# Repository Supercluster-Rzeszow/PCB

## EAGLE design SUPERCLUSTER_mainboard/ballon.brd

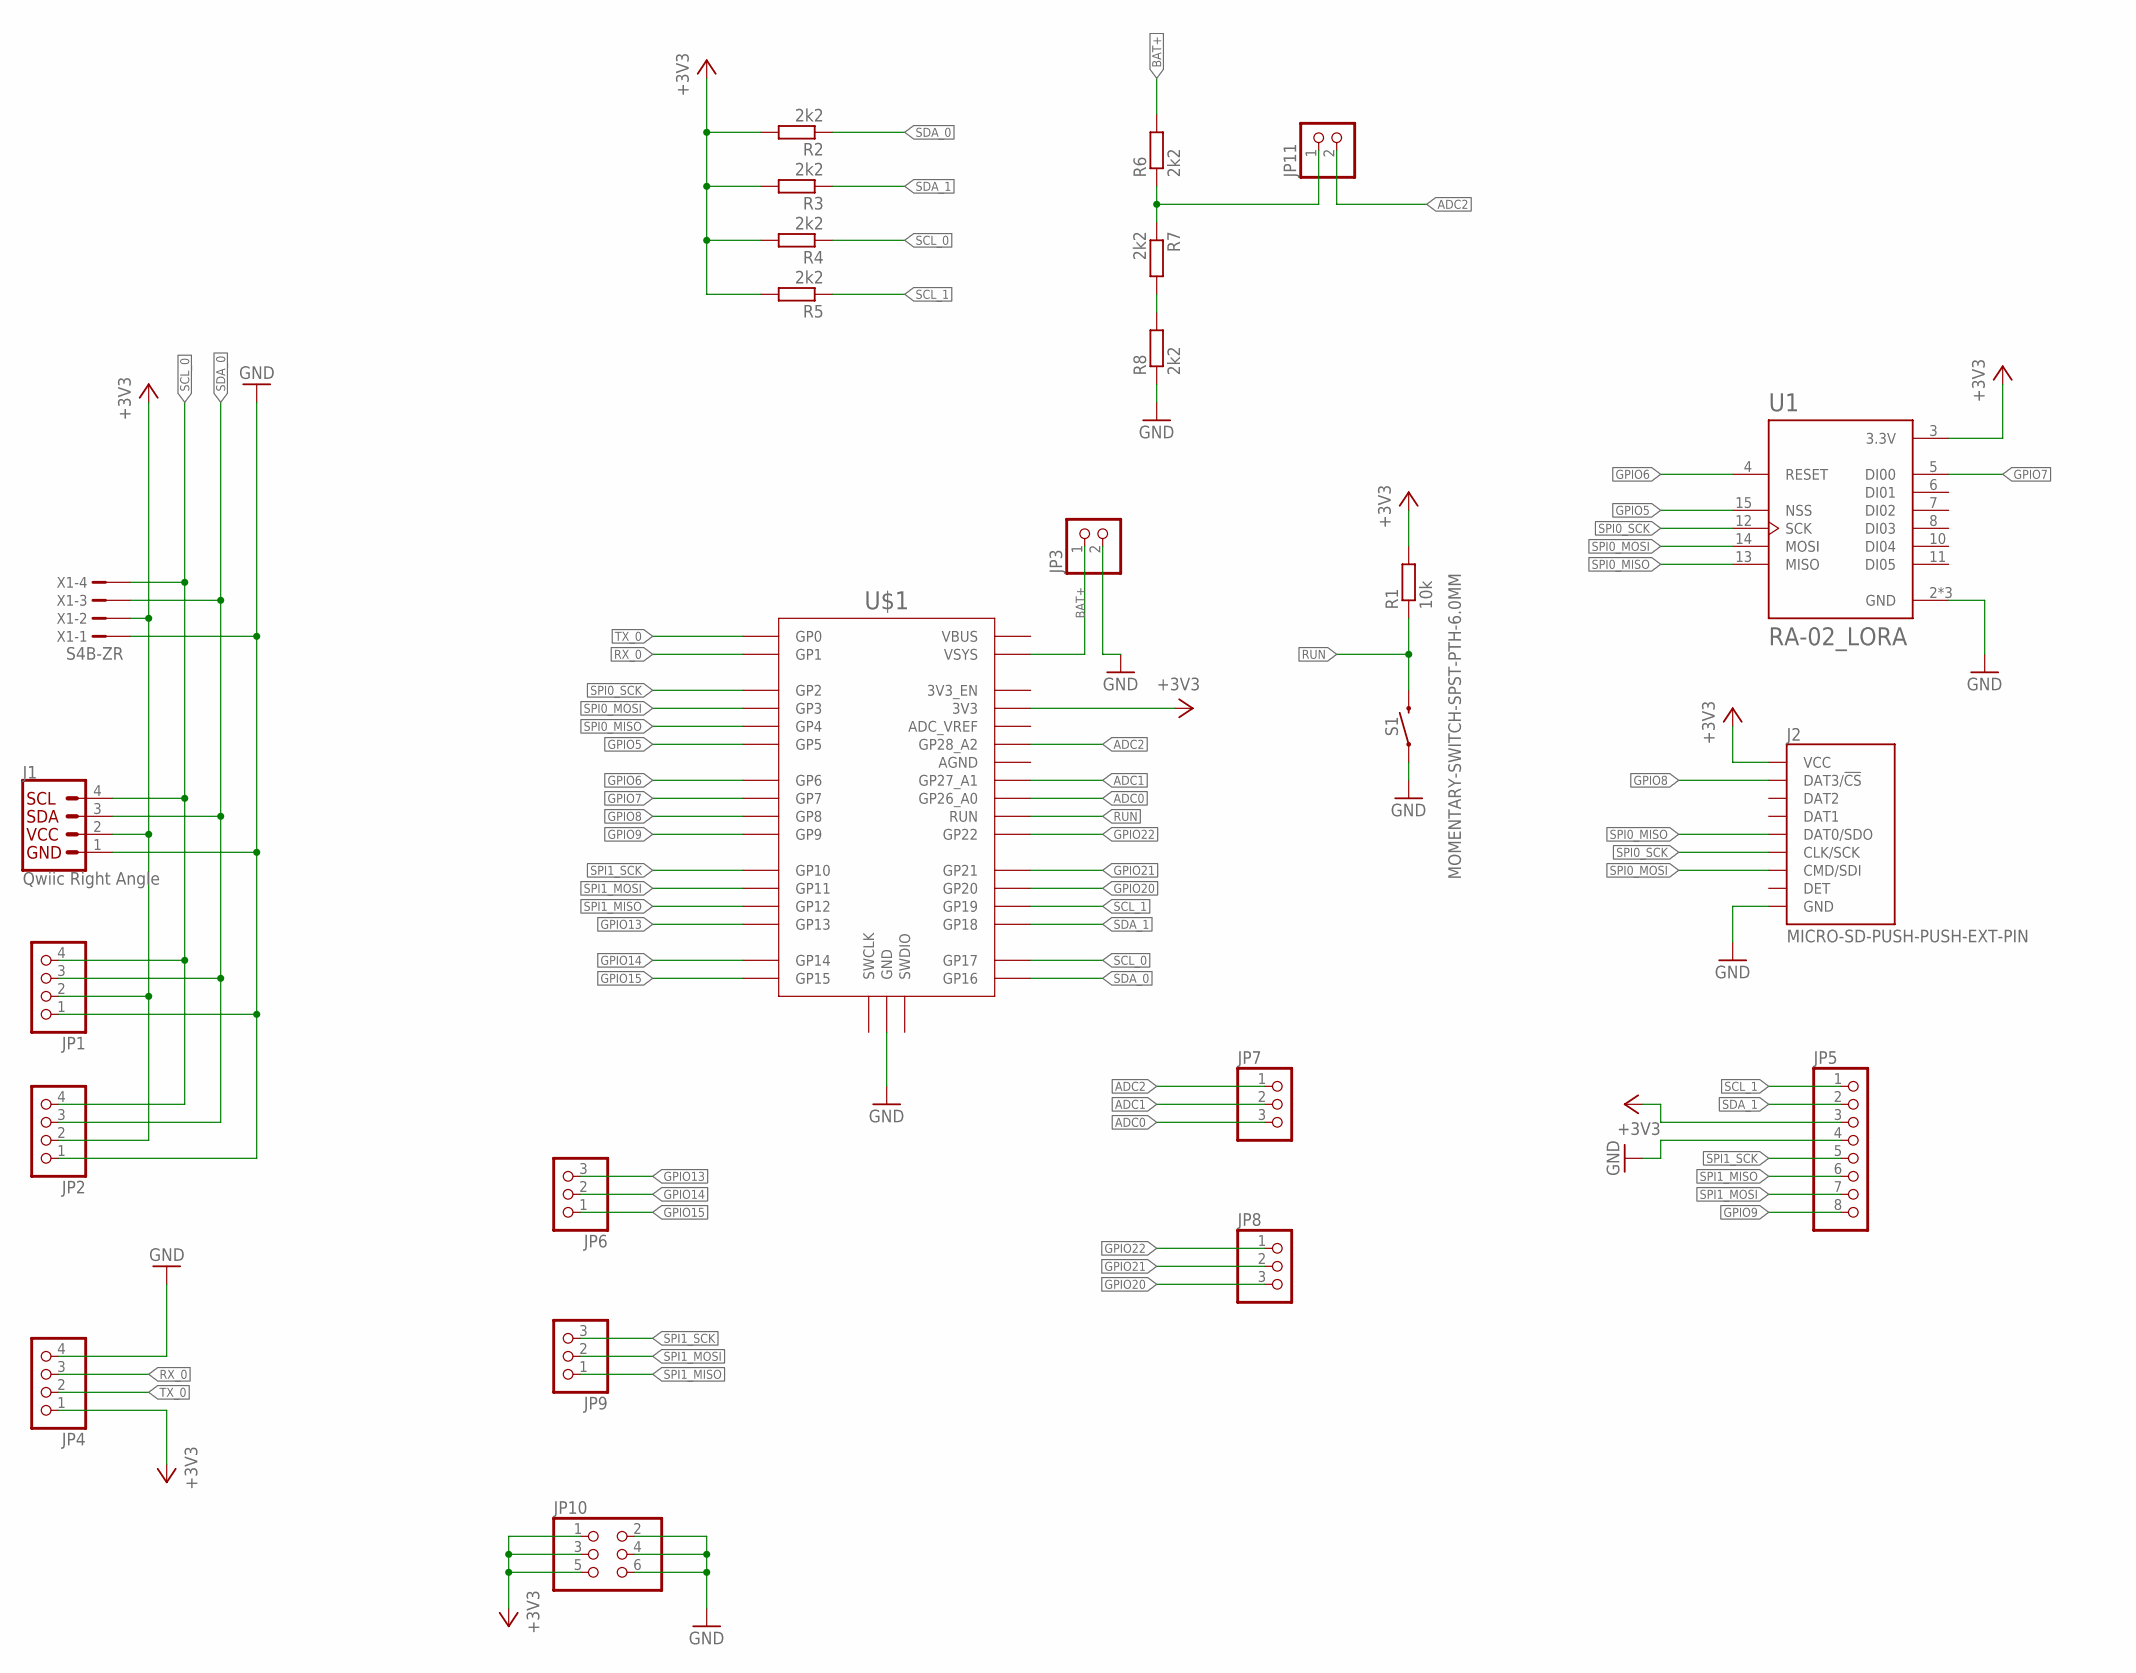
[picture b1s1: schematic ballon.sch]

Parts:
J1: Qwiic Right Angle; JST04_1MM_RA
J2: MICRO-SD-PUSH-PUSH-EXT-PIN; MICROSD-EXTERNALPIN
JP1, JP2, JP4: PINHD-1X4; 1X04
JP3, JP11: PINHD-1X2; 1X02
JP5: PINHD-1X8; 1X08
JP6, JP7, JP8, JP9: PINHD-1X3; 1X03
JP10: PINHD-2X3; 2X03
R1: 10k; 0204/7
R2, R3, R4, R5, R6, R7, R8: 2k2; 0204/7
S1: MOMENTARY-SWITCH-SPST-PTH-6.0MM; TACTILE_SWITCH_PTH_6.0MM
U1: RA-02_LORA; MODULE_RA-02_LORA
U$1: RPI_PICO-SMD; RPI_PICO
X1: S4B-ZR

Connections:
+3V3: J1.2, J2.4 (VCC), JP1.2, JP2.2, JP4.1, JP5.3, JP10.1, JP10.3, JP10.5, R1.2, R2.2, R3.2, R4.2, R5.2, U1.3 (3.3V), U$1.3V3, X1.2
ADC0: JP7.3, U$1.GP26_A0
ADC1: JP7.2, U$1.GP27_A1
ADC2: JP7.1, JP11.2, U$1.GP28_A2
BAT+: JP3.1, R6.2, U$1.VSYS
GND: J1.1, J2.6 (GND), J2.10 (GND), J2.11 (GND), J2.12 (GND), J2.13 (GND), JP1.1, JP2.1, JP3.2, JP4.4, JP5.4, JP10.2, JP10.4, JP10.6, R8.1, S1.1, U1.2 (GND), U1.9 (GND), U1.16 (GND), U$1.GND@1 (GND), U$1.GND@2 (GND), U$1.GND@3 (GND), U$1.GND@4 (GND), U$1.GND@5 (GND), U$1.GND@6 (GND), U$1.GND@7 (GND), U$1.GND@8 (GND), X1.1
GPIO5: U1.15 (NSS), U$1.GP5
GPIO6: U1.4 (RESET), U$1.GP6
GPIO7: U1.5 (DI00), U$1.GP7
GPIO8: J2.2 (DAT3/!CS!), U$1.GP8
GPIO9: JP5.8, U$1.GP9
GPIO13: JP6.3, U$1.GP13
GPIO14: JP6.2, U$1.GP14
GPIO15: JP6.1, U$1.GP15
GPIO20: JP8.3, U$1.GP20
GPIO21: JP8.2, U$1.GP21
GPIO22: JP8.1, U$1.GP22
unnamed: R7.2, R8.2
unnamed: JP11.1, R6.1, R7.1
RUN: R1.1, S1.3 (2), U$1.RUN
RX_0: JP4.3, U$1.GP1
SCL_0: J1.4, JP1.4, JP2.4, R4.1, U$1.GP17, X1.4
SCL_1: JP5.1, R5.1, U$1.GP19
SDA_0: J1.3, JP1.3, JP2.3, R2.1, U$1.GP16, X1.3
SDA_1: JP5.2, R3.1, U$1.GP18
SPI0_MISO: J2.7 (DAT0/SDO), U1.13 (MISO), U$1.GP4
SPI0_MOSI: J2.3 (CMD/SDI), U1.14 (MOSI), U$1.GP3
SPI0_SCK: J2.5 (CLK/SCK), U1.12 (SCK), U$1.GP2
SPI1_MISO: JP5.6, JP9.1, U$1.GP12
SPI1_MOSI: JP5.7, JP9.2, U$1.GP11
SPI1_SCK: JP5.5, JP9.3, U$1.GP10
TX_0: JP4.2, U$1.GP0

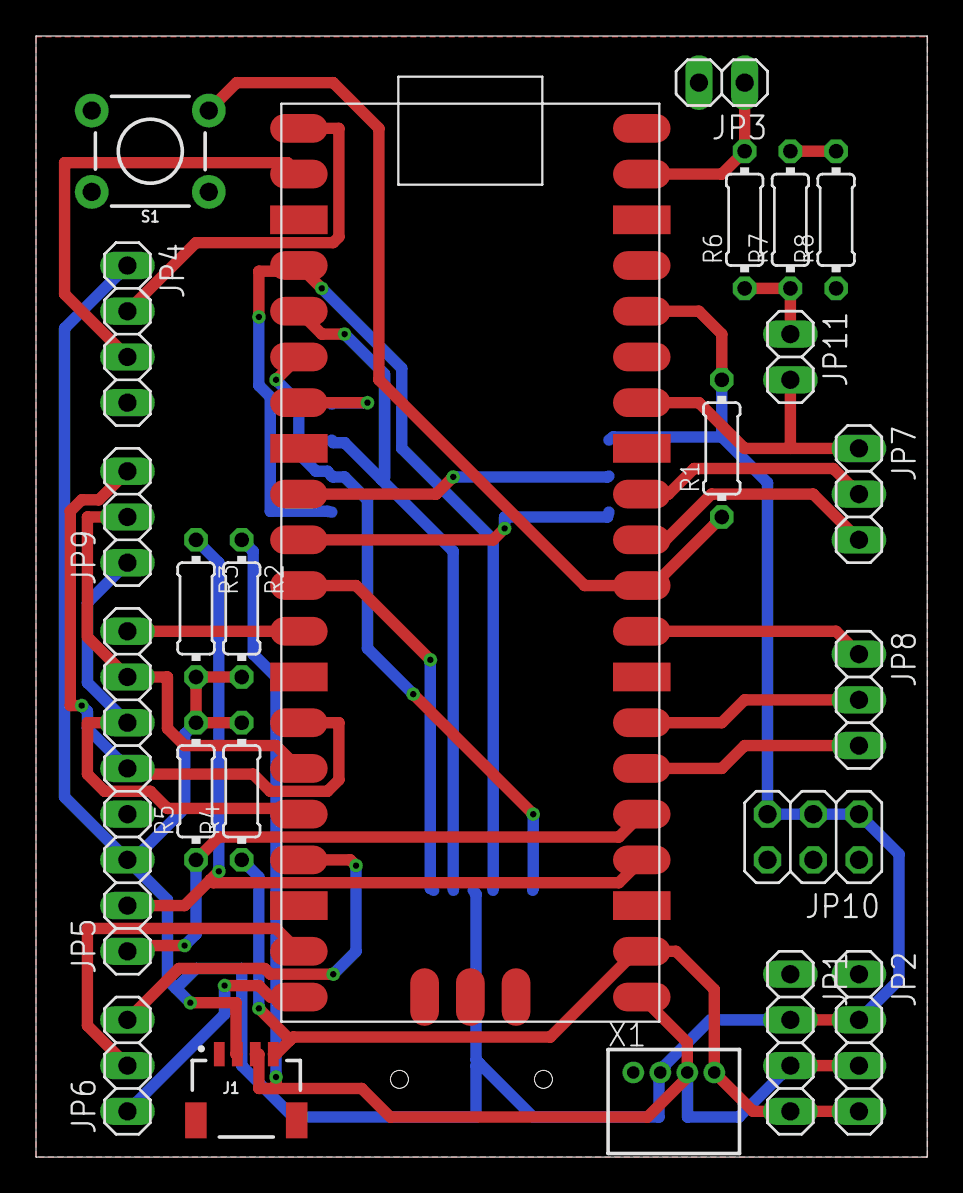
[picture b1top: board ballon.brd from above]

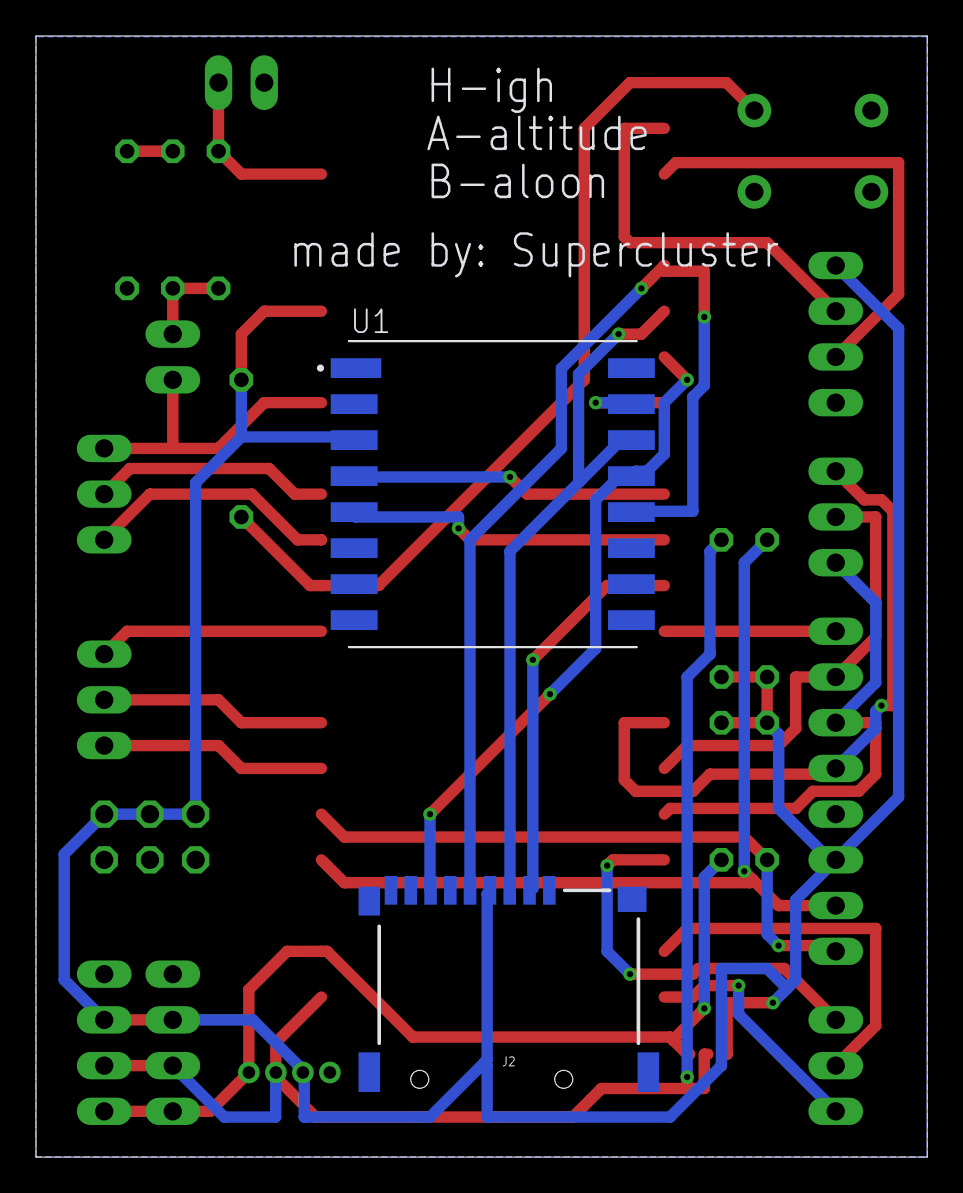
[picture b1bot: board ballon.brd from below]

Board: 2 copper layers, 49.5 x 62.3 mm, 25 parts (2 on the bottom side), 32 nets.

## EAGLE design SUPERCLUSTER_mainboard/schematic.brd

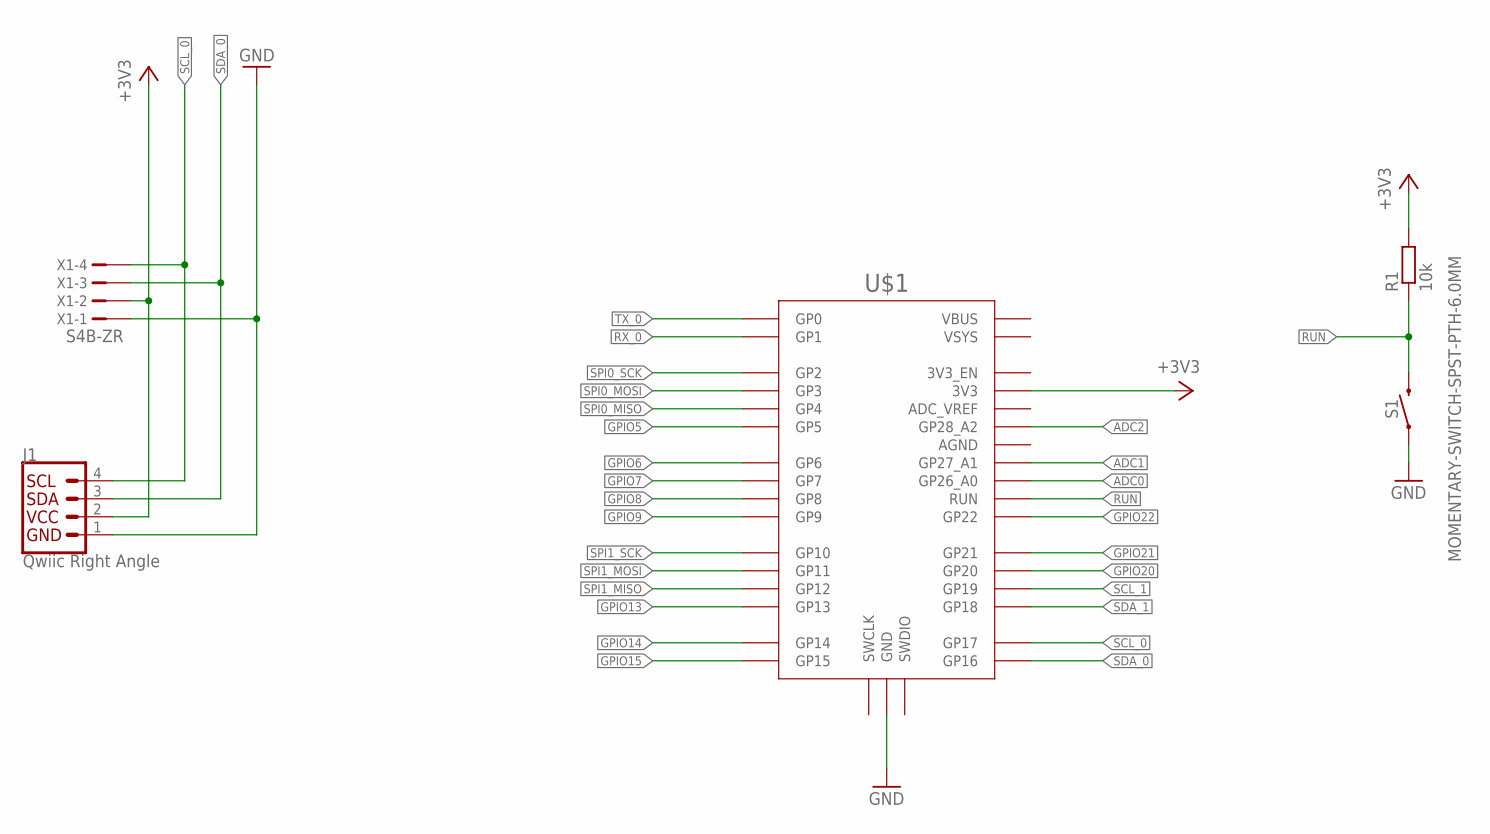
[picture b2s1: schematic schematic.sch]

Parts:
J1: Qwiic Right Angle; JST04_1MM_RA
R1: 10k; 0204/7
S1: MOMENTARY-SWITCH-SPST-PTH-6.0MM; TACTILE_SWITCH_PTH_6.0MM
U$1: RPI_PICO-SMD; RPI_PICO
X1: S4B-ZR

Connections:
+3V3: J1.2, R1.2, U$1.3V3, X1.2
ADC0: U$1.GP26_A0
ADC1: U$1.GP27_A1
ADC2: U$1.GP28_A2
GND: J1.1, S1.1, U$1.GND@1 (GND), U$1.GND@2 (GND), U$1.GND@3 (GND), U$1.GND@4 (GND), U$1.GND@5 (GND), U$1.GND@6 (GND), U$1.GND@7 (GND), U$1.GND@8 (GND), X1.1
GPIO5: U$1.GP5
GPIO6: U$1.GP6
GPIO7: U$1.GP7
GPIO8: U$1.GP8
GPIO9: U$1.GP9
GPIO13: U$1.GP13
GPIO14: U$1.GP14
GPIO15: U$1.GP15
GPIO20: U$1.GP20
GPIO21: U$1.GP21
GPIO22: U$1.GP22
RUN: R1.1, S1.3 (2), U$1.RUN
RX_0: U$1.GP1
SCL_0: J1.4, U$1.GP17, X1.4
SCL_1: U$1.GP19
SDA_0: J1.3, U$1.GP16, X1.3
SDA_1: U$1.GP18
SPI0_MISO: U$1.GP4
SPI0_MOSI: U$1.GP3
SPI0_SCK: U$1.GP2
SPI1_MISO: U$1.GP12
SPI1_MOSI: U$1.GP11
SPI1_SCK: U$1.GP10
TX_0: U$1.GP0

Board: 2 copper layers, 5 parts (0 on the bottom side), 5 nets, no tracks yet.

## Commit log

2021-10-02 PCB 0.1
2021-10-02 PCB 0.2
2021-10-02 PCB 0.3
2021-10-02 bom add
2021-10-02 truch removing
2021-10-03 PCB 1.0
    final touch
2021-10-03 PCB bugfix

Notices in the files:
parts and their libraries:
SparkFun-Connectors: Licensing: Creative Commons ShareAlike 4.0 International - https://creativecommons.org/licenses/by-sa/4.0
